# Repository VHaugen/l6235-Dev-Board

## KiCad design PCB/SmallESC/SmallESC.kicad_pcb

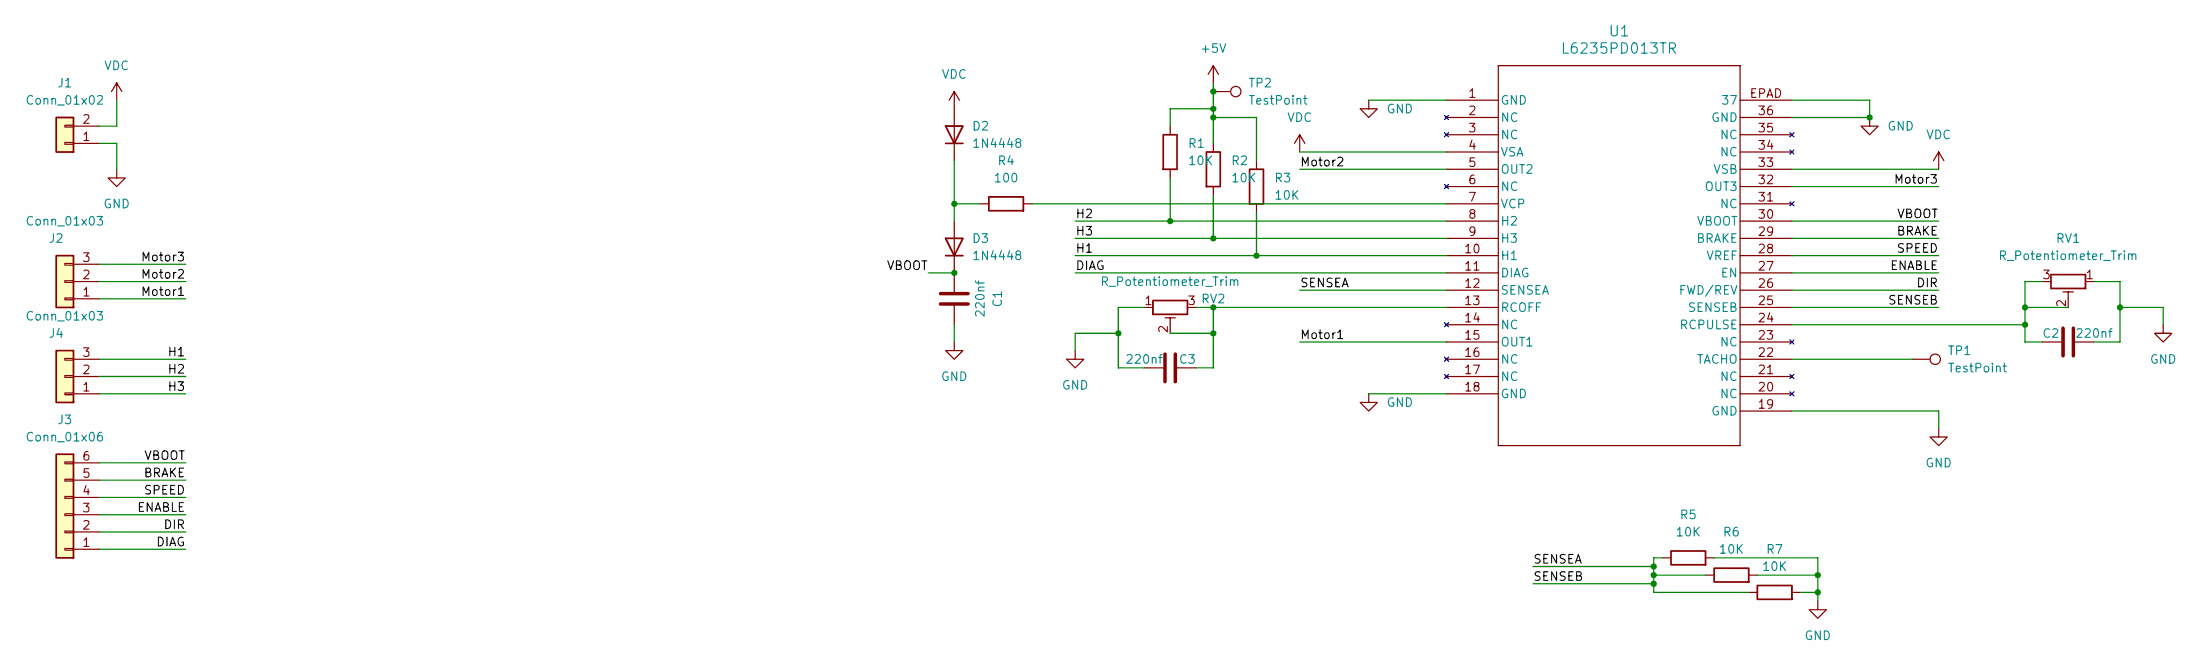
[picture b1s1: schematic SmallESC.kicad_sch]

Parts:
C1, C2, C3: 220nf; C_0805_2012Metric
D2, D3: 1N4448; D_DO-35_SOD27_P7.62mm_Horizontal
J1: Conn_01x02; TerminalBlock_RND_205-00001_1x02_P5.00mm_Horizontal
J2, J4: Conn_01x03; PinHeader_1x03_P2.54mm_Vertical
J3: Conn_01x06; PinHeader_1x06_P2.54mm_Vertical
R1, R2, R3, R5, R6, R7: 10K; R_0805_2012Metric_Pad1.20x1.40mm_HandSolder
R4: 100; R_0805_2012Metric_Pad1.20x1.40mm_HandSolder
RV1, RV2: R_Potentiometer_Trim; Potentiometer_Bourns_3266Z_Horizontal
TP1, TP2: TestPoint; TestPoint_Pad_1.0x1.0mm
U1: L6235PD013TR; PowerSO-36_STM

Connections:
+5V: R1.1, R2.1, R3.1, TP2.1; also elsewhere on the board
/BRAKE: J3.5, U1.29 (BRAKE)
/DIAG: J3.1, U1.11 (DIAG)
/DIR: J3.2, U1.26 (FWD/REV)
/ENABLE: J3.3, U1.27 (EN)
/H1: J4.3, R3.2, U1.10 (H1)
/H2: J4.2, R1.2, U1.8 (H2)
/H3: J4.1, R2.2, U1.9 (H3)
/Motor1: J2.1, U1.15 (OUT1)
/Motor2: J2.2, U1.5 (OUT2)
/Motor3: J2.3, U1.32 (OUT3)
/SENSEA: R5.1, R6.1, R7.1, U1.12 (SENSEA), U1.25 (SENSEB)
/SPEED: J3.4, U1.28 (VREF)
/VBOOT: C1.1, D3.1 (K), J3.6, U1.30 (VBOOT)
GND: C1.2, C2.2, C3.2, J1.1, R5.2, R6.2, R7.2, RV1.1, RV2.1, U1.1 (GND), U1.18 (GND), U1.19 (GND), U1.36 (GND), U1.EPAD (37)
unnamed: D2.1 (K), D3.2 (A), R4.1
unnamed: C3.1, RV2.2, RV2.3, U1.13 (RCOFF)
unnamed: C2.1, RV1.2, RV1.3, U1.24 (RCPULSE)
unnamed 18: TP1.1, U1.22 (TACHO); also elsewhere on the board
unnamed: R4.2, U1.7 (VCP)
VDC: D2.2 (A), J1.2, U1.4 (VSA), U1.33 (VSB)

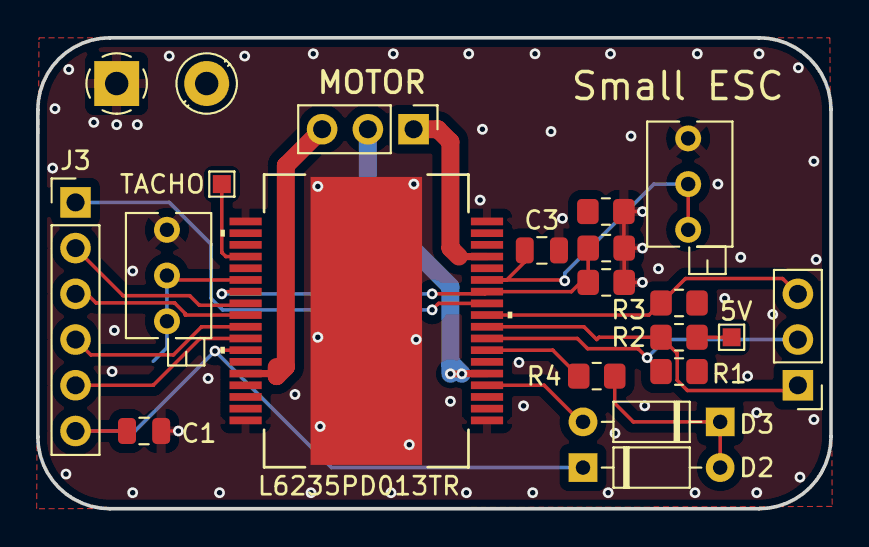
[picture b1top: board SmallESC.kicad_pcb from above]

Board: 4 copper layers, 44.1 x 26.2 mm, 21 parts (1 on the bottom side), 21 nets.

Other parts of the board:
5V: TestPoint; TestPoint_Pad_1.0x1.0mm
TACHO: TestPoint; TestPoint_Pad_1.0x1.0mm

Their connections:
+5V: 5V.1; also elsewhere on the board
unnamed 18: TACHO.1; also elsewhere on the board

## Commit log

2024-08-04 First protoype Order
